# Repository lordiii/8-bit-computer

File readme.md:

# Custom 8 Bit Computer

The KiCad project in this folder contains a high-level view of the Computer using KiCad's subschematics. 

_TODO: High-Level View as PDF_

### Folder Structure
- [Parts](parts/): Contains KiCad 5 schematics of each of the computers parts.
- [Instructions](instructions/): FPGA implementation of the instruction decoder, as well as the list of instructions 

### Credits
- [Ben Eater](https://eater.net). Some parts are based on his 8 Bit Computer

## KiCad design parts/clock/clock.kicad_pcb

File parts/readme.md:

### TODO
This folder will contain a list of each sub-part and a brief description

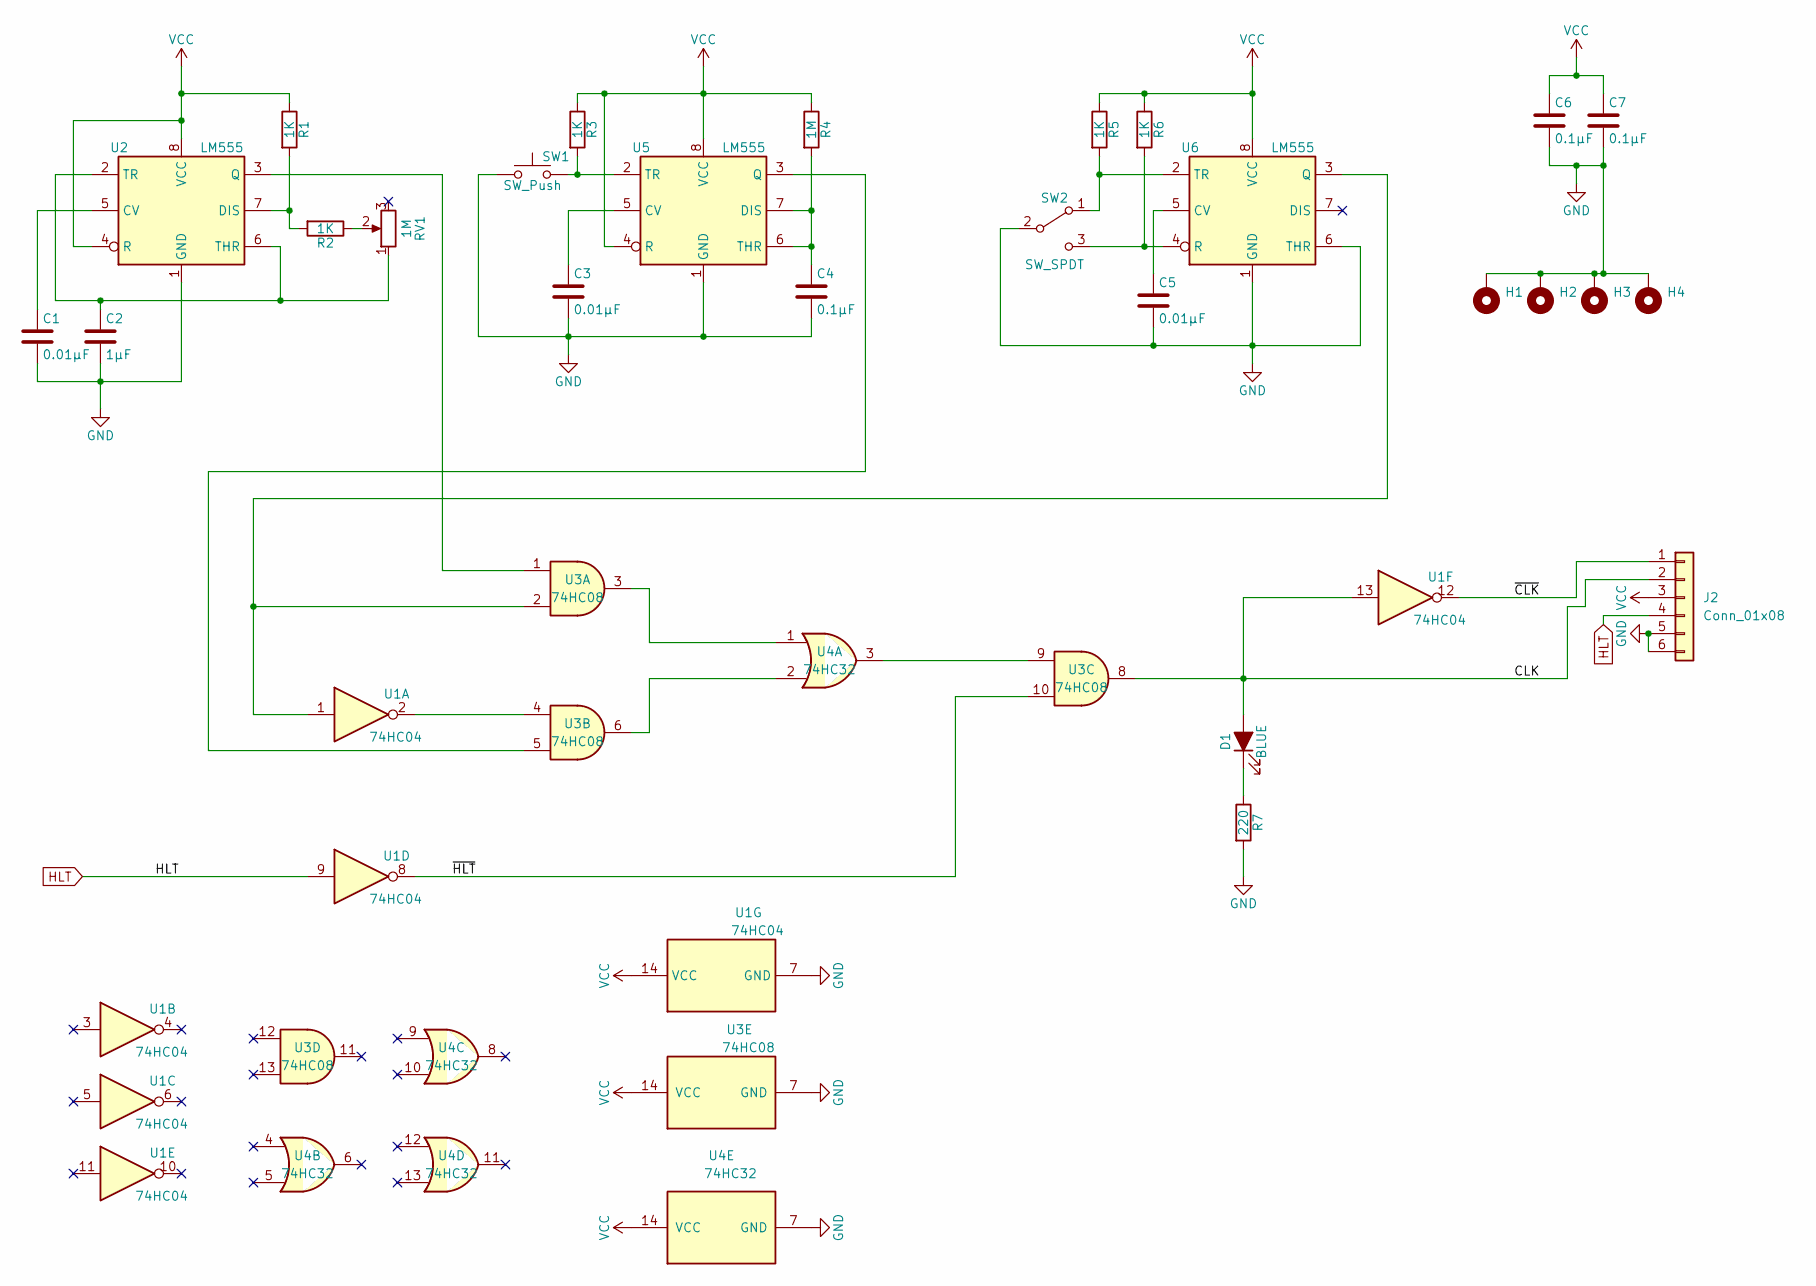
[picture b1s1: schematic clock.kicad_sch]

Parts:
C1, C3, C5: 0.01µF; C_0805_2012Metric
C2: 1µF; C_0805_2012Metric
C4, C6, C7: 0.1µF; C_0805_2012Metric
D1: BLUE; LED_0805_2012Metric
H1, H2, H3, H4: MountingHole_Pad; MountingHole_2.2mm_M2_DIN965_Pad
J2: Conn_01x08; IDC-Header_2x03_P2.54mm_Vertical
R1, R2, R3, R5, R6: 1K; R_0805_2012Metric
R4: 1M; R_0805_2012Metric
R7: 220; R_0805_2012Metric
RV1: 1M; Potentiometer_ACP_CA9-V10_Vertical
SW1: SW_Push; SW_PUSH-12mm
SW2: SW_SPDT; switch
U1: 74HC04; SO-14_3.9x8.65mm_P1.27mm
U2, U5, U6: LM555; SO-8_3.9x4.9mm_P1.27mm
U3: 74HC08; SO-14_3.9x8.65mm_P1.27mm
U4: 74HC32; SO-14_3.9x8.65mm_P1.27mm

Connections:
/CLK: D1.2 (A), J2.2, U1.13, U3.8
/~CLK: J2.1, U1.12
/~HLT: U1.8, U3.10
GND: C1.2, C2.2, C3.2, C4.2, C5.2, C6.2, C7.2, H1.1, H2.1, H3.1, H4.1, J2.5, J2.6, R7.2, SW1.1, SW2.2 (B), U1.7 (GND), U2.1 (GND), U3.7 (GND), U4.7 (GND), U5.1 (GND), U6.1 (GND), U6.6 (THR)
HLT: J2.4, U1.9
unnamed: C1.1, U2.5 (CV)
unnamed: C2.1, RV1.1, U2.2 (TR), U2.6 (THR)
unnamed: C3.1, U5.5 (CV)
unnamed: C4.1, R4.2, U5.6 (THR), U5.7 (DIS)
unnamed: C5.1, U6.5 (CV)
unnamed: D1.1 (K), R7.1
unnamed: R1.2, R2.2, U2.7 (DIS)
unnamed: R2.1, RV1.2
unnamed: R3.2, SW1.2, U5.2 (TR)
unnamed: R5.2, SW2.1 (A), U6.2 (TR)
unnamed: R6.2, SW2.3 (C), U6.4 (R)
unnamed: U1.1, U3.2, U6.3 (Q)
unnamed: U1.2, U3.4
unnamed: U2.3 (Q), U3.1
unnamed: U3.3, U4.1
unnamed: U3.5, U5.3 (Q)
unnamed: U3.6, U4.2
unnamed: U3.9, U4.3
VCC: C6.1, C7.1, J2.3, R1.1, R3.1, R4.1, R5.1, R6.1, U1.14 (VCC), U2.4 (R), U2.8 (VCC), U3.14 (VCC), U4.14 (VCC), U5.4 (R), U5.8 (VCC), U6.8 (VCC)

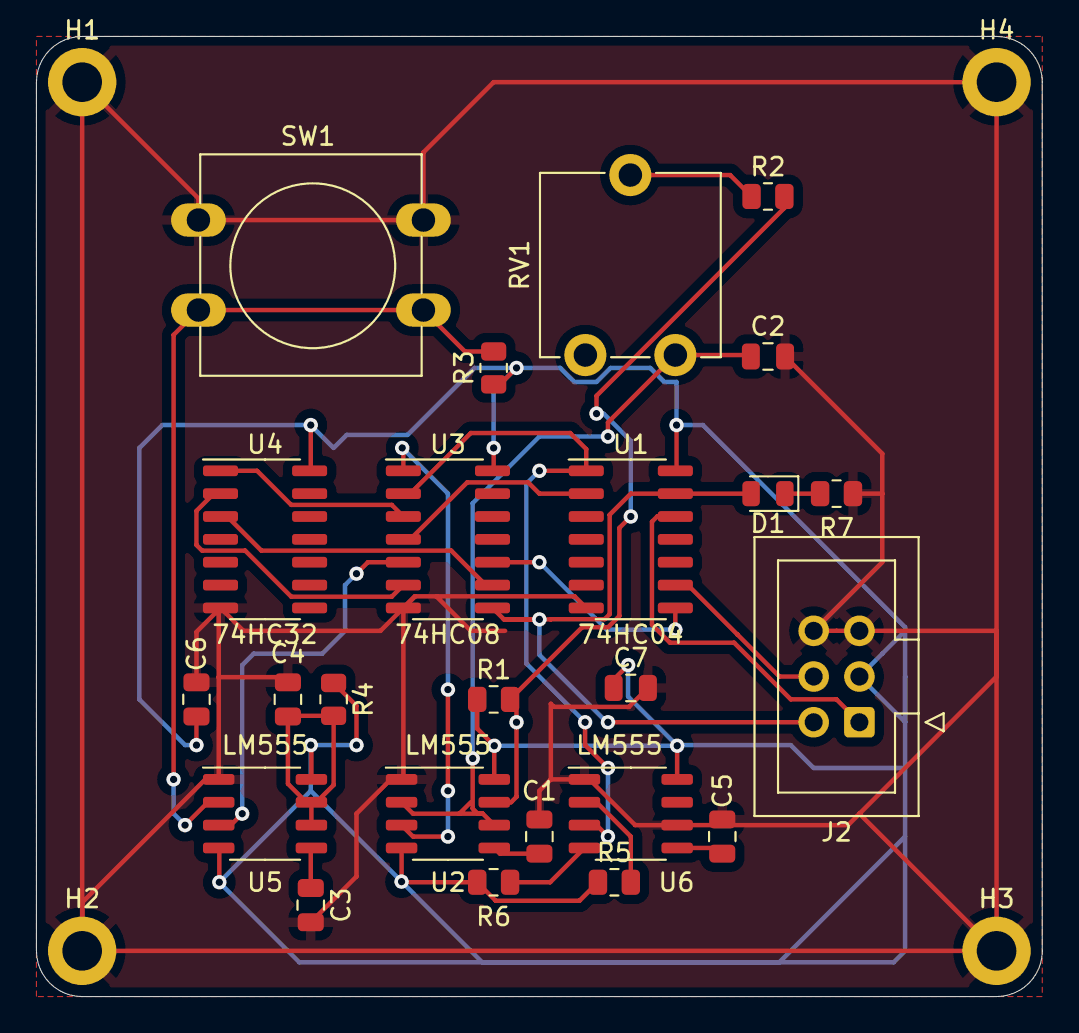
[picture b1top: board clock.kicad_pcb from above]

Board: 2 copper layers, 55.9 x 53.3 mm, 28 parts (0 on the bottom side), 24 nets.

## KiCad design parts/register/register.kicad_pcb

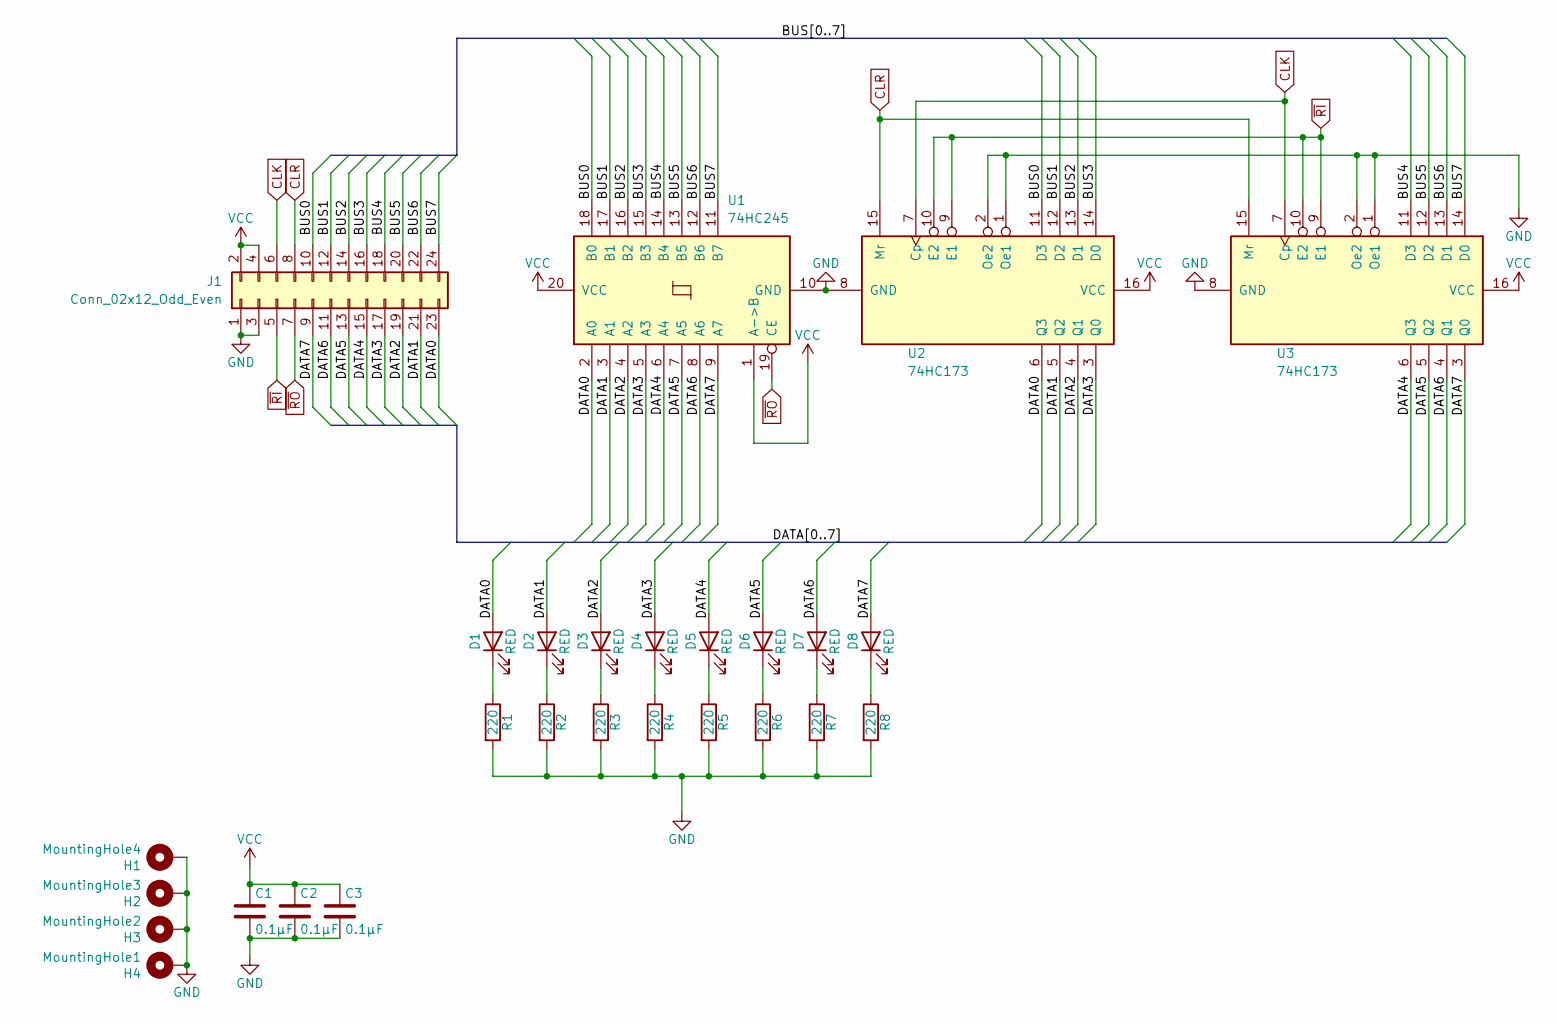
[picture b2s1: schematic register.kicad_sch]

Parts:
C1, C2, C3: 0.1µF; C_0805_2012Metric
D1, D2, D3, D4, D5, D6, D7, D8: RED; LED_0805_2012Metric
H1: MountingHole4; MountingHole_2.2mm_M2_Pad_Via
H2: MountingHole3; MountingHole_2.2mm_M2_Pad_Via
H3: MountingHole2; MountingHole_2.2mm_M2_Pad_Via
H4: MountingHole1; MountingHole_2.2mm_M2_Pad_Via
J1: Conn_02x12_Odd_Even; IDC-Header_2x12_P2.54mm_Vertical
R1, R2, R3, R4, R5, R6, R7, R8: 220; R_0805_2012Metric
U1: 74HC245; TSSOP-20_4.4x6.5mm_P0.65mm
U2, U3: 74HC173; SOIC-16_3.9x9.9mm_P1.27mm

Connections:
/BUS0: J1.10, U1.18 (B0), U2.11 (D3)
/BUS1: J1.12, U1.17 (B1), U2.12 (D2)
/BUS2: J1.14, U1.16 (B2), U2.13 (D1)
/BUS3: J1.16, U1.15 (B3), U2.14 (D0)
/BUS4: J1.18, U1.14 (B4), U3.11 (D3)
/BUS5: J1.20, U1.13 (B5), U3.12 (D2)
/BUS6: J1.22, U1.12 (B6), U3.13 (D1)
/BUS7: J1.24, U1.11 (B7), U3.14 (D0)
/DATA0: D1.2 (A), J1.23, U1.2 (A0), U2.6 (Q3)
/DATA1: D2.2 (A), J1.21, U1.3 (A1), U2.5 (Q2)
/DATA2: D3.2 (A), J1.19, U1.4 (A2), U2.4 (Q1)
/DATA3: D4.2 (A), J1.17, U1.5 (A3), U2.3 (Q0)
/DATA4: D5.2 (A), J1.15, U1.6 (A4), U3.6 (Q3)
/DATA5: D6.2 (A), J1.13, U1.7 (A5), U3.5 (Q2)
/DATA6: D7.2 (A), J1.11, U1.8 (A6), U3.4 (Q1)
/DATA7: D8.2 (A), J1.9, U1.9 (A7), U3.3 (Q0)
CLK: J1.6, U2.7 (Cp), U3.7 (Cp)
CLR: J1.8, U2.15 (Mr), U3.15 (Mr)
GND: C1.2, C2.2, C3.2, H1.1, H2.1, H3.1, H4.1, J1.1, J1.3, R1.2, R2.2, R3.2, R4.2, R5.2, R6.2, R7.2, R8.2, U1.10 (GND), U2.1 (Oe1), U2.2 (Oe2), U2.8 (GND), U3.1 (Oe1), U3.2 (Oe2), U3.8 (GND)
unnamed: D1.1 (K), R1.1
unnamed: D2.1 (K), R2.1
unnamed: D3.1 (K), R3.1
unnamed: D4.1 (K), R4.1
unnamed: D5.1 (K), R5.1
unnamed: D6.1 (K), R6.1
unnamed: D7.1 (K), R7.1
unnamed: D8.1 (K), R8.1
VCC: C1.1, C2.1, C3.1, J1.2, J1.4, U1.1 (A->B), U1.20 (VCC), U2.16 (VCC), U3.16 (VCC)
~RI: J1.5, U2.9 (E1), U2.10 (E2), U3.9 (E1), U3.10 (E2)
~RO: J1.7, U1.19 (CE)

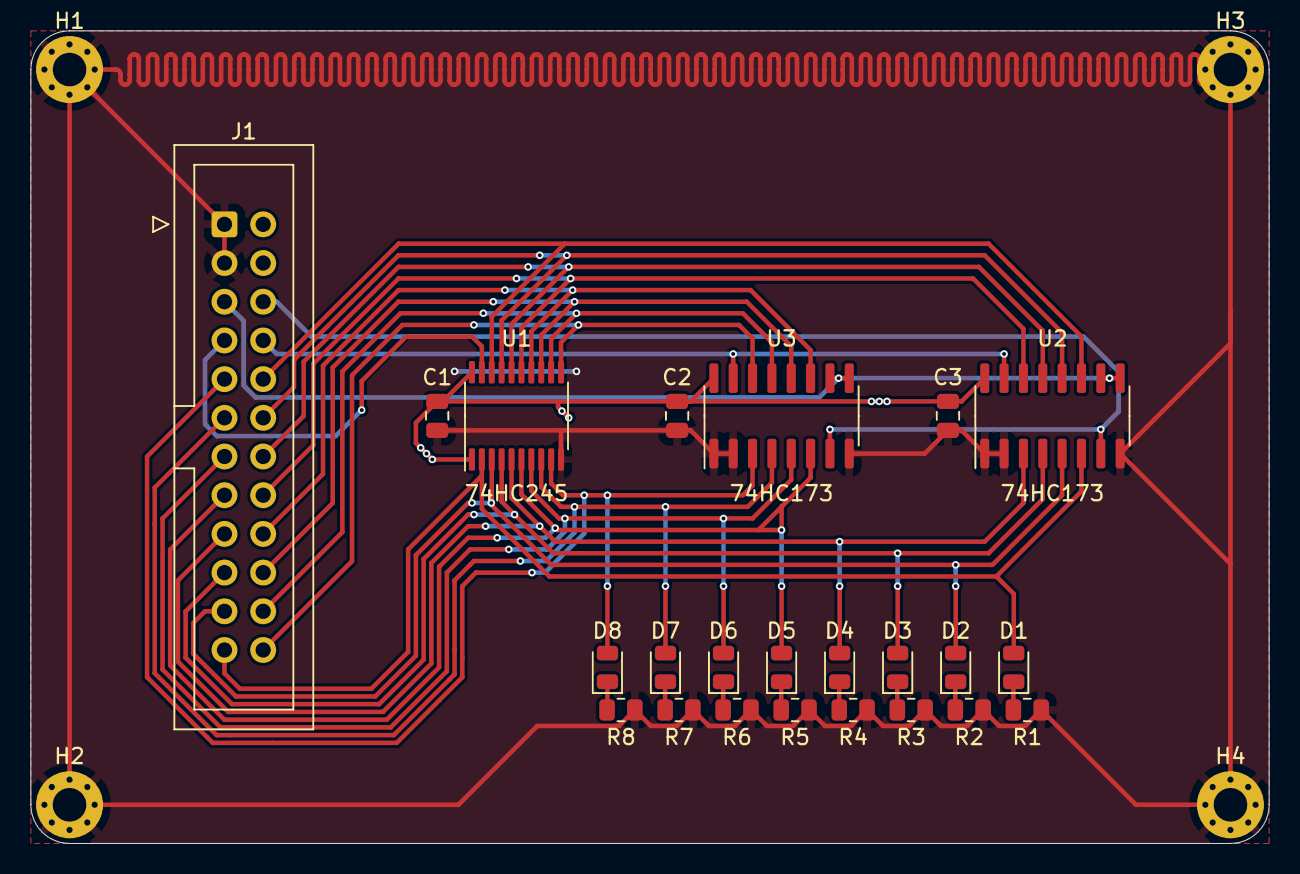
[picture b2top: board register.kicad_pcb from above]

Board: 2 copper layers, 81.3 x 53.3 mm, 27 parts (0 on the bottom side), 30 nets.

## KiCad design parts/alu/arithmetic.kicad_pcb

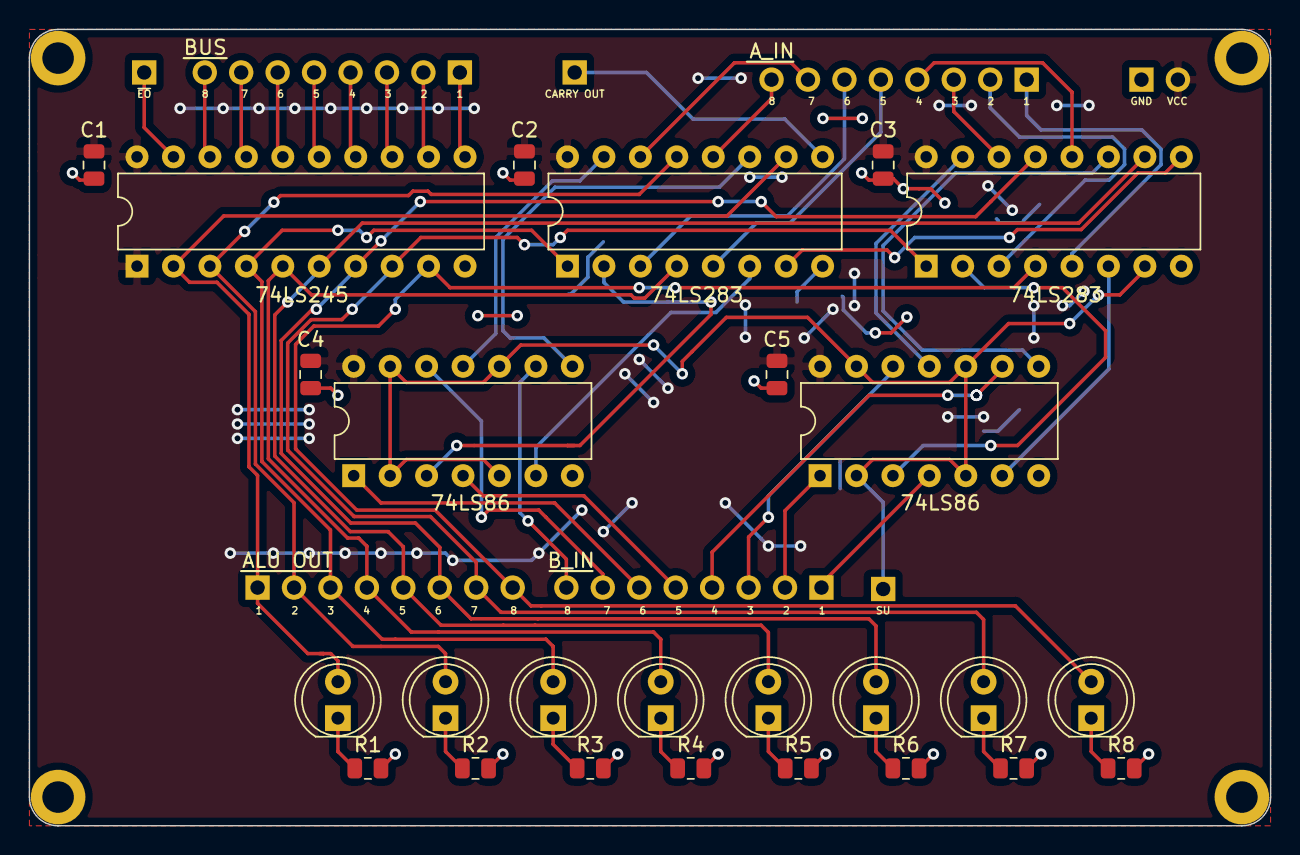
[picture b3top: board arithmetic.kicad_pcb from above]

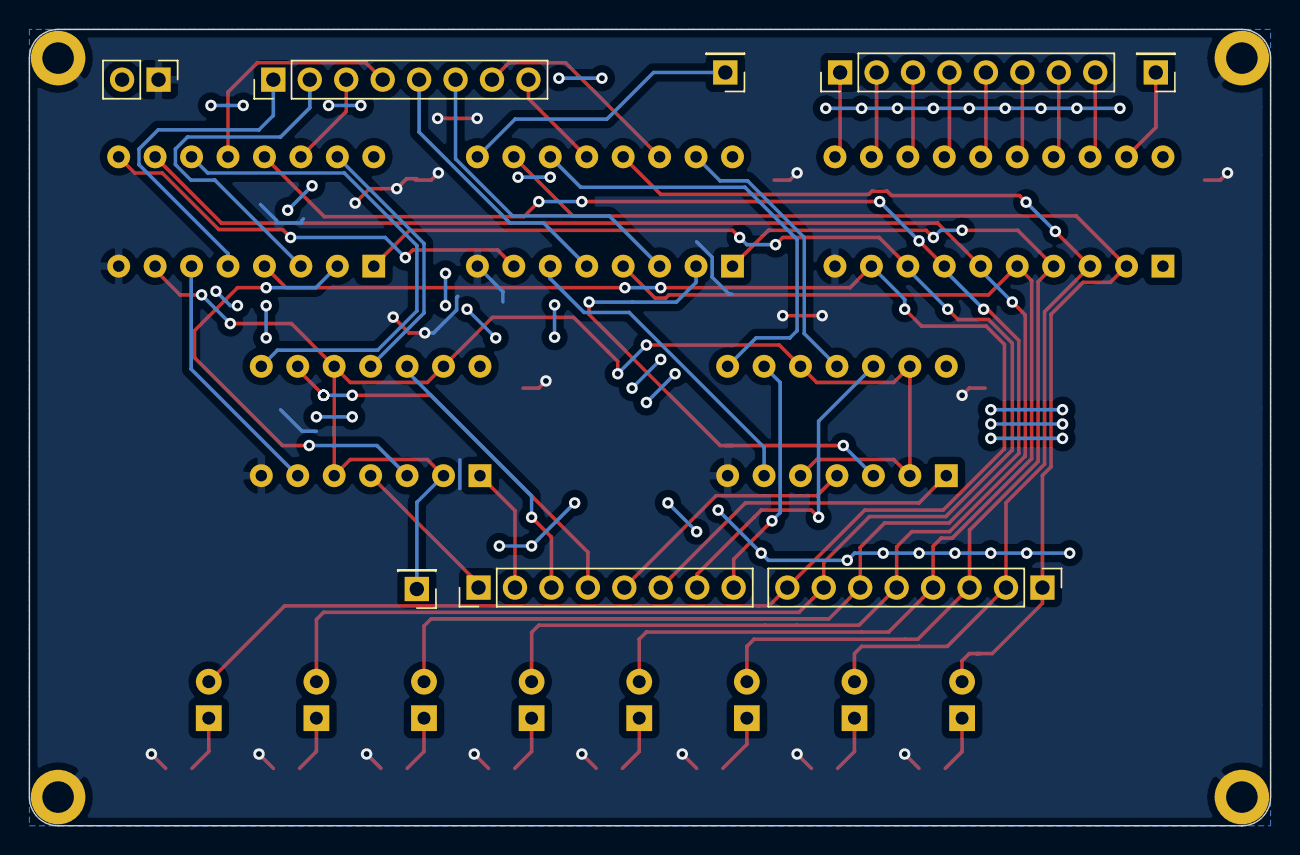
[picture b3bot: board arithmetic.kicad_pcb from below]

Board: 2 copper layers, 86.5 x 55.5 mm, 38 parts (8 on the bottom side), 54 nets.

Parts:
C1, C2, C3, C4, C5: 0.1µF; C_0805_2012Metric
D1, D2, D3, D4, D5, D6, D7, D8: RED; LED_D5.0mm
H1, H2, H3, H4: MountingHole_Pad; MountingHole_2.2mm_M2_DIN965_Pad
J1: ~{EO}; PinHeader_1x01_P2.54mm_Vertical
J2: SU; PinHeader_1x01_P2.54mm_Vertical
J3: BUS; PinHeader_1x08_P2.54mm_Vertical
J4: B_IN; PinHeader_1x08_P2.54mm_Vertical
J5: CARRY OUT; PinHeader_1x01_P2.54mm_Vertical
J6: A_IN; PinHeader_1x08_P2.54mm_Vertical
J7: ALU OUT; PinHeader_1x08_P2.54mm_Vertical
J8: Conn_01x02; PinHeader_1x02_P2.54mm_Vertical
R1, R2, R3, R4, R5, R6, R7, R8: 220; R_0805_2012Metric
U1, U3: 74LS86; DIP-14_W7.62mm
U2: 74LS245; DIP-20_W7.62mm
U4, U5: 74LS283; DIP-16_W7.62mm

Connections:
/A1: J6.8, U4.12 (A4)
/A2: J6.7, U4.14 (A3)
/A3: J6.6, U4.3 (A2)
/A4: J6.5, U4.5 (A1)
/A5: J6.4, U5.12 (A4)
/A6: J6.3, U5.14 (A3)
/A7: J6.2, U5.3 (A2)
/A8: J6.1, U5.5 (A1)
/B1: J4.8, U1.9
/B2: J4.7, U1.12
/B3: J4.6, U1.1
/B4: J4.5, U1.4
/B5: J4.4, U3.9
/B6: J4.3, U3.12
/B7: J4.2, U3.1
/B8: J4.1, U3.4
/COUT: J5.1, U4.9 (C4)
/OUT1: D1.2 (A), J7.1, U2.2 (A0), U4.10 (S4)
/OUT2: D2.2 (A), J7.2, U2.3 (A1), U4.13 (S3)
/OUT3: D3.2 (A), J7.3, U2.4 (A2), U4.1 (S2)
/OUT4: D4.2 (A), J7.4, U2.5 (A3), U4.4 (S1)
/OUT5: D5.2 (A), J7.5, U2.6 (A4), U5.10 (S4)
/OUT6: D6.2 (A), J7.6, U2.7 (A5), U5.13 (S3)
/OUT7: D7.2 (A), J7.7, U2.8 (A6), U5.1 (S2)
/OUT8: D8.2 (A), J7.8, U2.9 (A7), U5.4 (S1)
/SU: J2.1, U1.2, U1.5, U1.10, U1.13, U3.2, U3.5, U3.10, U3.13, U5.7 (C0)
/~EO: J1.1, U2.19 (CE)
GND: C1.2, C2.2, C3.2, C4.2, C5.2, H1.1, H2.1, H3.1, H4.1, J8.1, R1.2, R2.2, R3.2, R4.2, R5.2, R6.2, R7.2, R8.2, U1.7 (GND), U2.10 (GND), U3.7 (GND), U4.8 (GND), U5.8 (GND)
unnamed: D1.1 (K), R1.1
unnamed: D2.1 (K), R2.1
unnamed: D3.1 (K), R3.1
unnamed: D4.1 (K), R4.1
unnamed: D5.1 (K), R5.1
unnamed: D6.1 (K), R6.1
unnamed: D7.1 (K), R7.1
unnamed: D8.1 (K), R8.1
unnamed: J3.1, U2.11 (B7)
unnamed: J3.2, U2.12 (B6)
unnamed: J3.3, U2.13 (B5)
unnamed: J3.4, U2.14 (B4)
unnamed: J3.5, U2.15 (B3)
unnamed: J3.6, U2.16 (B2)
unnamed: J3.7, U2.17 (B1)
unnamed: J3.8, U2.18 (B0)
unnamed: U1.3, U4.2 (B2)
unnamed: U1.6, U4.6 (B1)
unnamed: U1.8, U4.11 (B4)
unnamed: U1.11, U4.15 (B3)
unnamed: U3.3, U5.2 (B2)
unnamed: U3.6, U5.6 (B1)
unnamed: U3.8, U5.11 (B4)
unnamed: U3.11, U5.15 (B3)
unnamed: U4.7 (C0), U5.9 (C4)
VCC: C1.1, C2.1, C3.1, C4.1, C5.1, J8.2, U1.14 (VCC), U2.1 (A->B), U2.20 (VCC), U3.14 (VCC), U4.16 (VCC), U5.16 (VCC)

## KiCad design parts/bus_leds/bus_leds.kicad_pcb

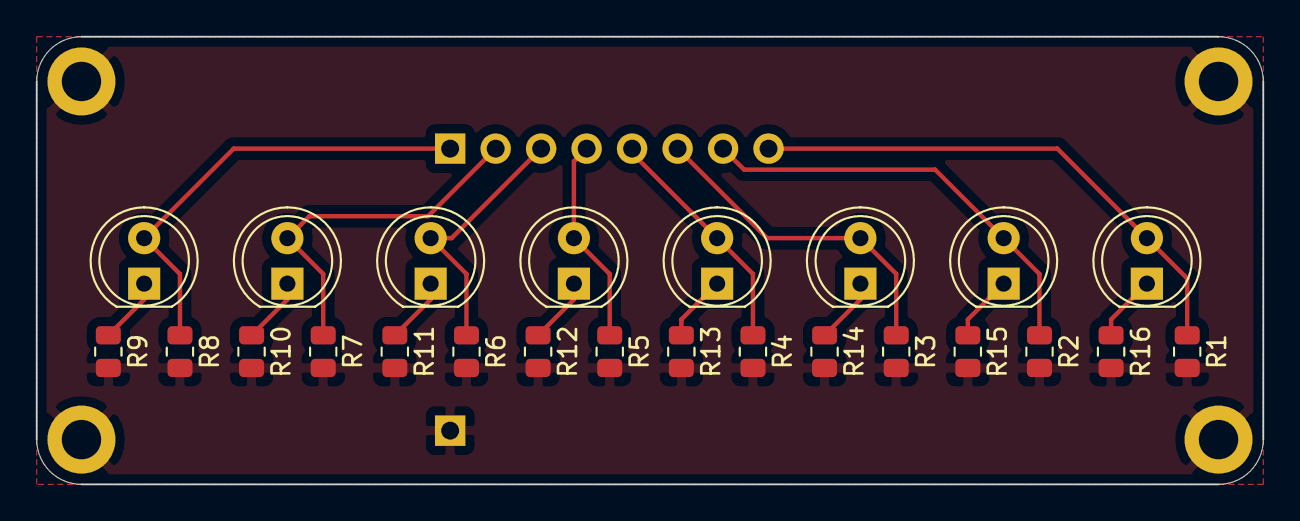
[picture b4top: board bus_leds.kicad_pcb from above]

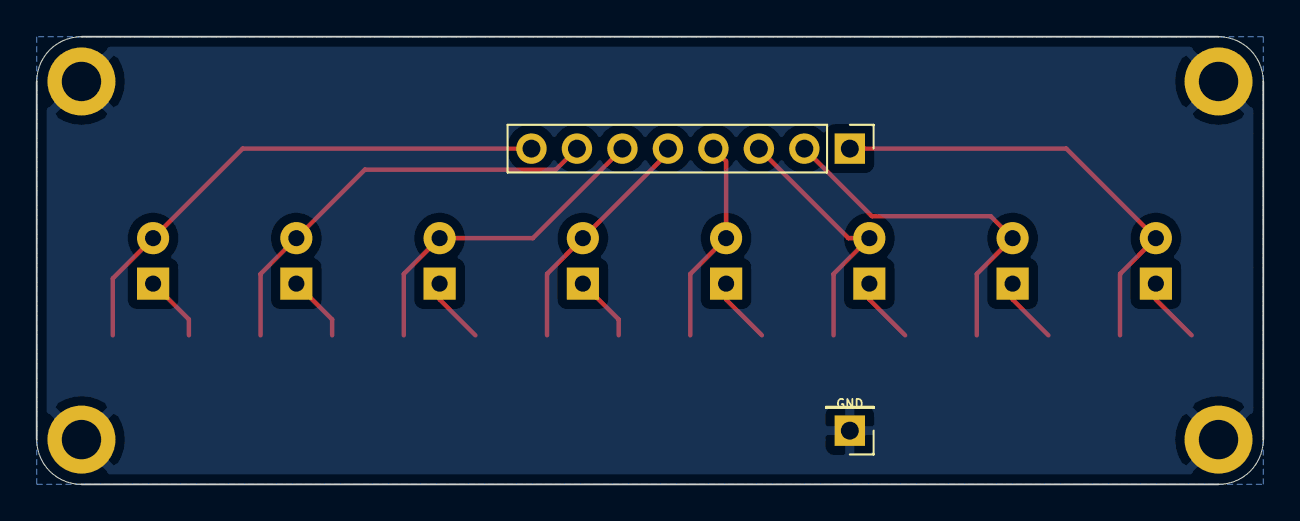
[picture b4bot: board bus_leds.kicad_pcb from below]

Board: 2 copper layers, 68.5 x 25.0 mm, 30 parts (2 on the bottom side), 17 nets.

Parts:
D1, D2, D3, D4, D5, D6, D7, D8: RED; LED_D5.0mm
H1, H2, H3, H4: MountingHole_Pad; MountingHole_2.2mm_M2_DIN965_Pad
J1: BUS; PinHeader_1x08_P2.54mm_Vertical
J2: GND; PinHeader_1x01_P2.54mm_Vertical
R1, R2, R3, R4, R5, R6, R7, R8: 10k; R_0805_2012Metric
R9, R10, R11, R12, R13, R14, R15, R16: 220; R_0805_2012Metric

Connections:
/BUS_0: D1.2, J1.1, R8.1
/BUS_1: D2.2, J1.2, R7.1
/BUS_2: D3.2, J1.3, R6.1
/BUS_3: D4.2, J1.4, R5.1
/BUS_4: D5.2, J1.5, R4.1
/BUS_5: D6.2, J1.6, R3.1
/BUS_6: D7.2, J1.7, R2.1
/BUS_7: D8.2, J1.8, R1.1
GND: H1.1, H2.1, H3.1, H4.1, J2.1, R1.2, R2.2, R3.2, R4.2, R5.2, R6.2, R7.2, R8.2, R9.2, R10.2, R11.2, R12.2, R13.2, R14.2, R15.2, R16.2
unnamed: D1.1, R9.1
unnamed: D2.1, R10.1
unnamed: D3.1, R11.1
unnamed: D4.1, R12.1
unnamed: D5.1, R13.1
unnamed: D6.1, R14.1
unnamed: D7.1, R15.1
unnamed: D8.1, R16.1

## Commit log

2022-05-11 Readme Files
2022-05-11 Update Instruction Ranges
2022-06-20 Prepare Verilog
2022-06-20 Start Pin Definition
2022-06-20 Prepare Makefile
2022-06-20 Add CBUS Pins
2022-06-20 Test Verilog
2022-06-20 Fix Comments
2022-06-20 Change Instruction Ranges
2022-06-21 Define Instruction Groups
2022-06-21 Update Instructions
2022-06-21 Update High Level
2022-06-27 Architecture v1
2022-06-28 Update Architecture
2022-06-28 SMD Register
2022-06-29 Create PCB for Register
2022-07-15 SMD Clock
